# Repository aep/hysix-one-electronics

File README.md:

Hysix One
=================

An Arduino compatible long runtime GSM sensor board.
The board is designed for use cases where the MCU remains mostly idle, then switches on in regular intervals to collect data and talk to the internet.

Features
-----
- Two external sensors with each 2 data lines can be connected and powered from the board.
- GSM module can be powered off completely independant from system power
- Ultra low power RTC switches entire board power (except RTC itself) for very long idle runtime.
- Arduino IDE compatible.

Mappings
-----
<table>
    <tr>
        <td>SIM800L RX</td>
        <td>7</td>
        <td></td>
    </tr>
    <tr>
        <td>SIM800L TX</td>
        <td>8</td>
        <td></td>
    </tr>
    <tr>
        <td>SIM800L Enable Power</td>
        <td>9</td>
        <td>switch power to the SIM</td>
    </tr>
    <tr>
        <td>LDO_ENABLE</td>
        <td>10</td>
        <td>enable line for the LDO supplying the avr</td>
    </tr>
    <tr>
        <td>BATTER_METER</td>
        <td>A0</td>
        <td>raw battery voltage divided by two</td>
    </tr>
    <tr>
        <td>BATTER_METER_ENABLE</td>
        <td>2</td>
        <td>pull low to enable voltage divider</td>
    </tr>
    <tr>
        <td>SENSOR PINS</td>
        <td>3,4,5,6,</td>
        <td>data lines on the sensor connectors </td>
    </tr>
    <tr>
        <td>RTC</td>
        <td>I2C</td>
        <td>RTC is on standard I2C bus</td>
    </tr>
</table>

Stats
-----

<table>
    <tr>
        <td>Peak Power</td>
        <td>200mA</td>
    </tr>
    <tr>
        <td>Idle Power</td>
        <td>11mA</td>
    </tr>
    <tr>
        <td>RTC Standby Power</td>
        <td> &lt; 1uA </td>
    </tr>
</table>

RTC
-----

The RTC is a DS134X TDFN at I2C address 0x68 that switches the entire system off, keeps a clock, and switches it back on at a desired time.
In the default solder jumper configuration, it has INTB connected to LDO enable, inverted by a transistor,
so that high means LDO is on, which is the default in shipping state.
The avr remains powered until the RTC gets interupt enable set.

Visual
-------
size aprox 5x5cm

Design Notes
-------

- The Diodes in front of the RTC are supposed to drop voltage from BAT to max 5V. There is no extra regulator, because the RTC is fairly tolerant.
- There's no routing to the reset pin of the SIM800. To use the FONA library, it needs to have the reset code removed.
- The reset button turns the avr ON when the RTC switched the system off. Make sure to reset the RTC fairly early so that system stays on after releasing the button.

License
-------
http://opensource.org/licenses/MIT

Bugs
------

1. Forgot to route reset without the arduino cap.
   To burn a bootloader, reset needs to be soldered onto the MCU side of R2 instead of using the pin header.
   During normal arduino 'uploading', the pins will work fine.

2. The connector parts in the scheme don't actually fit. Ignore them and use bare pin headers.

3. LDO_ENABLE is a wasted pin. The RTC is already enabling the LDO. It's probably a good idea to leave SJ4 open.

4. Forgot resistors for RX on the SIM800. The SIM800 is speced at max 3.1V TTL. Works fine, but...

5. The package for the Crystal is wrong. It's an SMD package, but the layout is for through hole.
   It fits sort of anyway. Originally i intended to run the avr without crystal, but the factory tunings for
   the internal clock are for 3.3V, not for 5V. A nightmare not worth it.

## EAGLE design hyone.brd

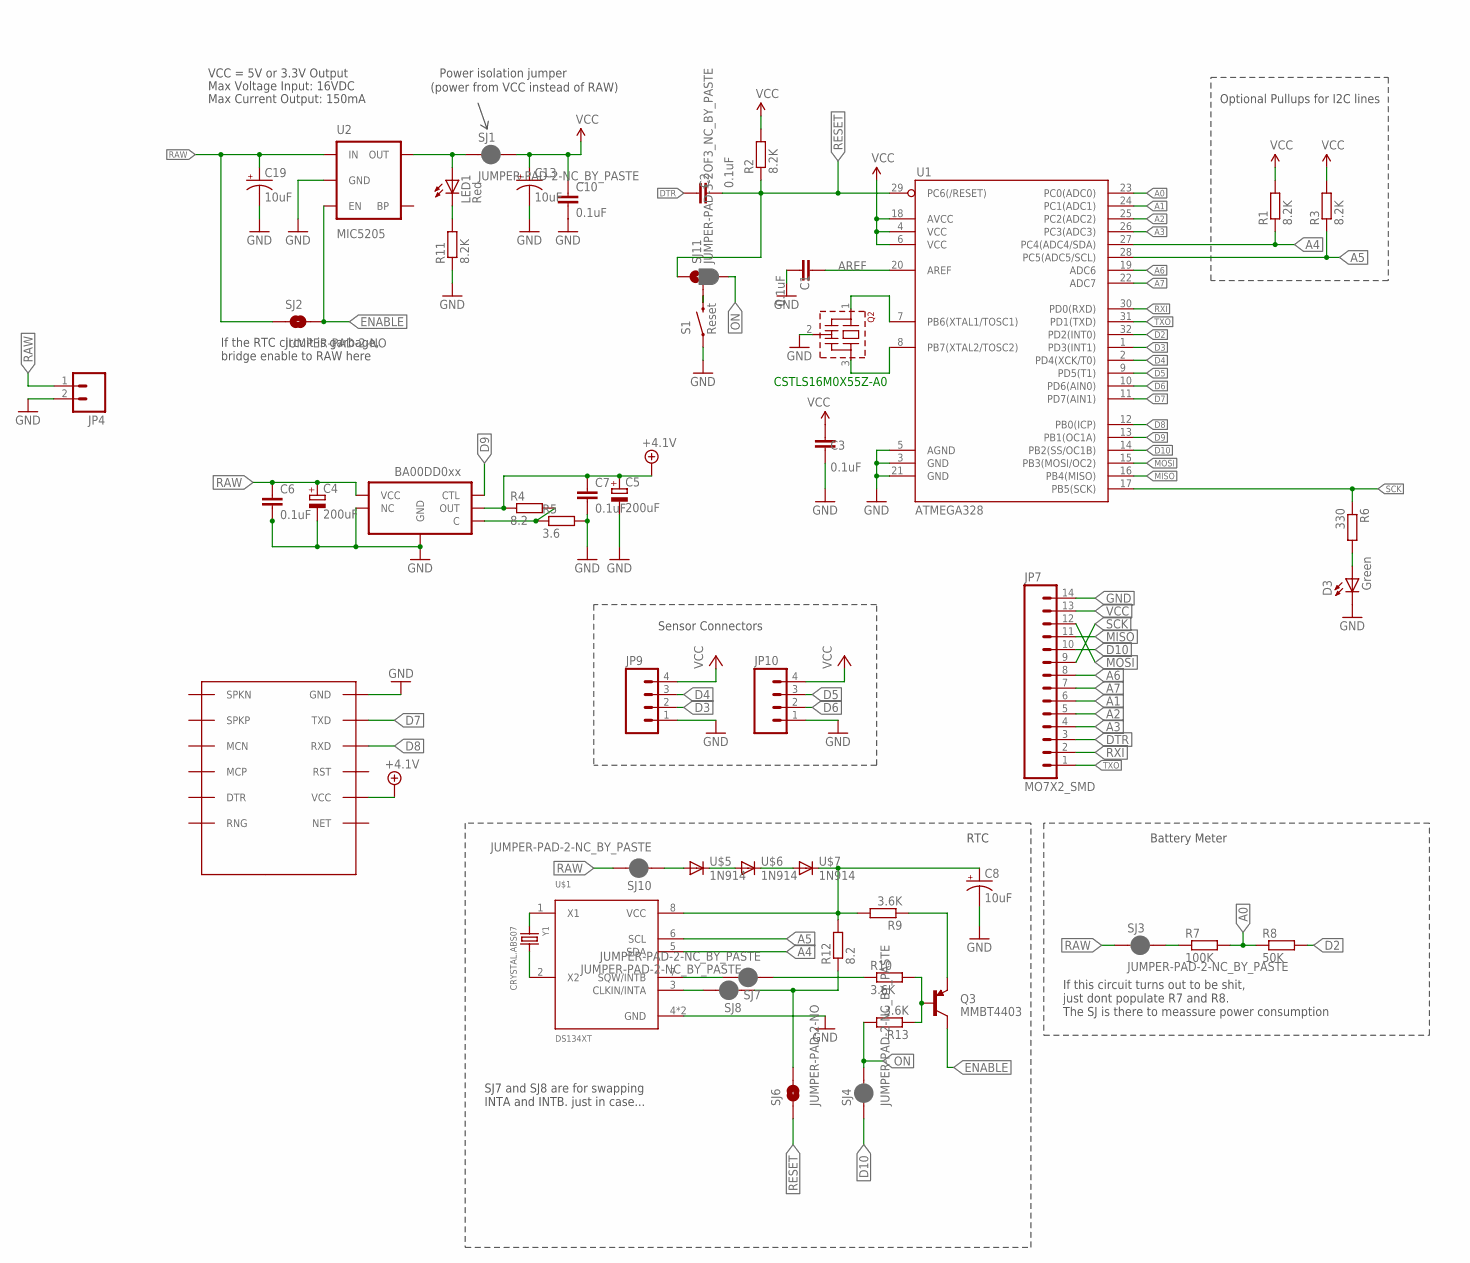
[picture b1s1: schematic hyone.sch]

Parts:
C1, C2, C3, C6, C7, C10: 0.1uF; C0805
C4, C5: 200uF; E5-5
C8, C13, C19: 10uF; EIA3216
D3: Green; CHIPLED_0805
JP4: M02POLAR; MOLEX-1X2
JP7: MO7X2_SMD; 2X7_SMD
JP9, JP10: M04POLAR; MOLEX-1X4
LED1: Red; CHIPLED_0805
Q2: CSTLS_X
Q3: MMBT4403; SOT23-3
R1, R2, R3, R11: 8.2K; R1206
R4, R12: 8.2; R1206
R5: 3.6; R1206
R6: 330; R1206
R7: 100K; R1206
R8: 50K; R1206
R9, R10, R13: 3.6K; R1206
S1: Reset; TACTILE-SWITCH-SMD-ALT01
SJ1, SJ3, SJ4, SJ7, SJ8, SJ10: JUMPER-PAD-2-NC_BY_PASTE; PAD-JUMPER-2-NC_BY_PASTE_YES_SILK
SJ2, SJ6: JUMPER-PAD-2-NO; PAD-JUMPER-2-NO_NO_SILK
SJ11: JUMPER-PAD-3-2OF3_NC_BY_PASTE; PAD-JUMPER-3-2OF3_NC_BY_PASTE_YES_SILK_FULL_BOX
U1: ATMEGA328; TQFP32-08
U2: MIC5205; SOT23-5
U$1: DS134XT; TDFN-8
U$2: BA00DD0XX; HRP5
U$4: SIM800L; SIM-CORE
U$5, U$6, U$7: 1N914; SOT23
Y1: CRYSTAL.ABS07; ABS07

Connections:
123123: SJ10.1, U$5.1 (A)
+4.1V: C5.+, C7.1, R4.1, U$2.4 (OUT), U$4.VCC
A0: R7.2, R8.1, U1.23 (PC0(ADC0))
A1: JP7.6, U1.24 (PC1(ADC1))
A2: JP7.5, U1.25 (PC2(ADC2))
A3: JP7.4, U1.26 (PC3(ADC3))
A4: R1.1, U1.27 (PC4(ADC4/SDA)), U$1.5 (SDA)
A5: R3.1, U1.28 (PC5(ADC5/SCL)), U$1.6 (SCL)
A6: JP7.8, U1.19 (ADC6)
A7: JP7.7, U1.22 (ADC7)
AREF: C1.2, U1.20 (AREF)
D2: R8.2, U1.32 (PD2(INT0))
D3: JP9.2, U1.1 (PD3(INT1))
D4: JP9.3, U1.2 (PD4(XCK/T0))
D5: JP10.3, U1.9 (PD5(T1))
D6: JP10.2, U1.10 (PD6(AIN0))
D7: U1.11 (PD7(AIN1)), U$4.TXD
D8: U1.12 (PB0(ICP)), U$4.RXD
D9: U1.13 (PB1(OC1A)), U$2.1 (CTL)
D10: JP7.10, SJ4.1, U1.14 (PB2(SS/OC1B))
DTR: C2.2, JP7.3
ENABLE: Q3.3 (C), SJ2.2, U2.3 (EN)
GND: C1.1, C3.1, C4.-, C5.-, C6.2, C7.2, C8.C (-), C10.2, C13.C (-), C19.C (-), D3.C, JP4.2, JP7.14, JP9.1, JP10.1, Q2.2 (VSS), R5.2, R11.1, S1.1, S1.2 (1), U1.3 (GND), U1.5 (AGND), U1.21 (GND), U2.2 (GND), U$1.4 (GND), U$1.EP (GND), U$2.3 (NC), U$2.6 (GND), U$4.GND
MISO: JP7.11, U1.16 (PB4(MISO))
MOSI: JP7.12, U1.15 (PB3(MOSI/OC2))
unnamed: Q2.1, U1.7 (PB6(XTAL1/TOSC1))
unnamed: Q2.3, U1.8 (PB7(XTAL2/TOSC2))
unnamed: LED1.A, SJ1.1, U2.5 (OUT)
unnamed: LED1.C, R11.2
unnamed: R4.2, R5.1, U$2.5 (C)
unnamed: U$1.1 (X1), Y1.1
unnamed: D3.A, R6.2
unnamed: U$1.2 (X2), Y1.2
unnamed: Q3.2 (E), R9.1
unnamed: Q3.1 (B), R10.2, R13.1
unnamed: C8.A (+), R9.2, R12.2, U$1.8 (VCC), U$7.3 (C)
unnamed: R10.1, SJ7.1
unnamed: R7.1, SJ3.2
unnamed: S1.3 (2), S1.4 (2), SJ11.2
unnamed: R12.1, SJ6.2, SJ8.1
unnamed: SJ7.2, U$1.7 (SQW/INTB)
unnamed: SJ8.2, U$1.3 (CLKIN/INTA)
unnamed: U$5.3 (C), U$6.1 (A)
unnamed: U$6.3 (C), U$7.1 (A)
ON: R13.2, SJ4.2, SJ11.3
RAW: C4.+, C6.1, C19.A (+), JP4.1, SJ2.1, SJ3.1, SJ10.2, U2.1 (IN), U$2.2 (VCC)
RESET: C2.1, R2.1, SJ6.1, SJ11.1, U1.29 (PC6(/RESET))
RXI: JP7.2, U1.30 (PD0(RXD))
SCK: JP7.9, R6.1, U1.17 (PB5(SCK))
TXO: JP7.1, U1.31 (PD1(TXD))
VCC: C3.2, C10.1, C13.A (+), JP7.13, JP9.4, JP10.4, R1.2, R2.2, R3.2, SJ1.2, U1.4 (VCC), U1.6 (VCC), U1.18 (AVCC)

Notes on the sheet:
Max Voltage Input: 16VDC
Max Current Output: 150mA
VCC = 5V or 3.3V Output
Optional Pullups for I2C lines
RTC
Power isolation jumper
(power from VCC instead of RAW)
Battery Meter
Sensor Connectors
If the RTC circuit is garbage, bridge enable to RAW here
If this circuit turns out to be shit, just dont populate R7 and R8. The SJ is there to meassure power consumption
SJ7 and SJ8 are for swapping INTA and INTB. just in case...
CSTLS16M0X55Z-A0

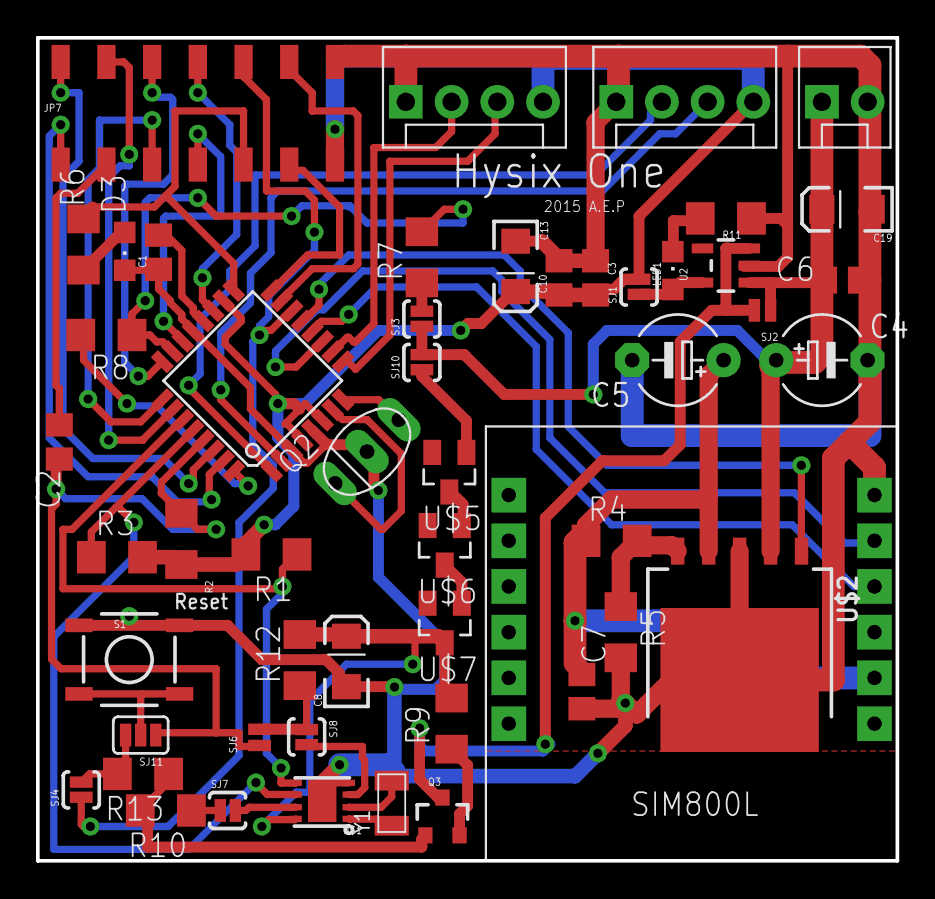
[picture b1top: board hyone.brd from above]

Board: 2 copper layers, 47.8 x 45.7 mm, 52 parts (1 on the bottom side), 51 nets.

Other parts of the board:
U$3: OSHW-LOGOS; OSHW-LOGO-S

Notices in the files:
parts and their libraries:
SparkFun-Passives: Licensing: CC v3.0 Share-Alike You are welcome to use this library for commercial purposes.
rohm-semi: Copyright (C) 2010, Bob Starr
SparkFun-Connectors: Licensing: Creative Commons ShareAlike 4.0 International - https://creativecommons.org/licenses/by-sa/4.0
